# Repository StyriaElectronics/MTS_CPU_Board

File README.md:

# 🧠 MTS_CPU_Board

The **MTS_CPU_Board** is the central controller card for the **Modular Test System (MTS)**, built around the Raspberry Pi CM4.  
It serves as the master board for communication and control of all plug-in modules via the MTS backplane.

---

---

## 📦 Features

- 🧠 Raspberry Pi CM4 for computing and control
- 🔌 Backplane interface: UART, SPI, I²C, GPIO, CAN
- 🚀 EtherCAT interface for high-speed real-time data exchange
- 📡 Automatic plug-in module registration and configuration via CAN bus
- ⚡ Power input with regulation and monitoring
- 🌐 Optional Web UI (Flask based)

---

## 📁 Repository Structure

```
MTS_CPU_Board/
├── hardware/       → KiCad project files
├── software/       → UART daemons, webserver, protocols
├── docs/           → Block diagrams, pinouts, descriptions
├── images/         → Project photos and preview graphics
├── LICENSE         → Project license (CC BY 4.0)
├── .gitignore      → Exclude temp files (KiCad, Python, etc.)
└── README.md       → You are here
```

---

## 📷 Preview
**Todo**
> Add preview images to `images/preview.png`  
> and insert them like this:

```markdown

```

---

## 🛠 Usage Ideas

- Slot management for plug-in cards
- Monitoring voltages / temperatures
- Logging & remote access via web
- UART/CAN message routing
- High-speed real-time data logging and control via EtherCAT

---

## 📃 License

📢 Commercial Use Available

This project is licensed under the **Creative Commons Attribution-NonCommercial 4.0 International (CC BY-NC 4.0)**.

You may freely use, modify, and distribute this work for non-commercial purposes only, provided appropriate credit is given to the author.

➡️ Commercial use, including but not limited to:
  -	Integration into commercial products or services
	-	Redistribution or sale of derived products or components
	-	Commercial consulting or deployment

**is strictly prohibited without explicit written permission**

If you intend to use this project commercially, please contact me directly to negotiate a suitable license agreement.

📬 Contact: [andras.nagy@styria-electronics.at]
---

⚠️ **Disclaimer:**
This project is provided "as is" without warranty of any kind, either expressed or implied, including but not limited to fitness for a particular purpose, functionality, accuracy, or non-infringement. In no event shall the author(s) be liable for any claim, damages, or other liability arising from, out of, or in connection with the use or other dealings in this project.

## 🤝 Contributing

Contributions are welcome! Fork this repo and feel free to open pull requests or issues.

## 🚀 Status

🔧 In development – basic structure in place.  
More hardware and software coming soon.

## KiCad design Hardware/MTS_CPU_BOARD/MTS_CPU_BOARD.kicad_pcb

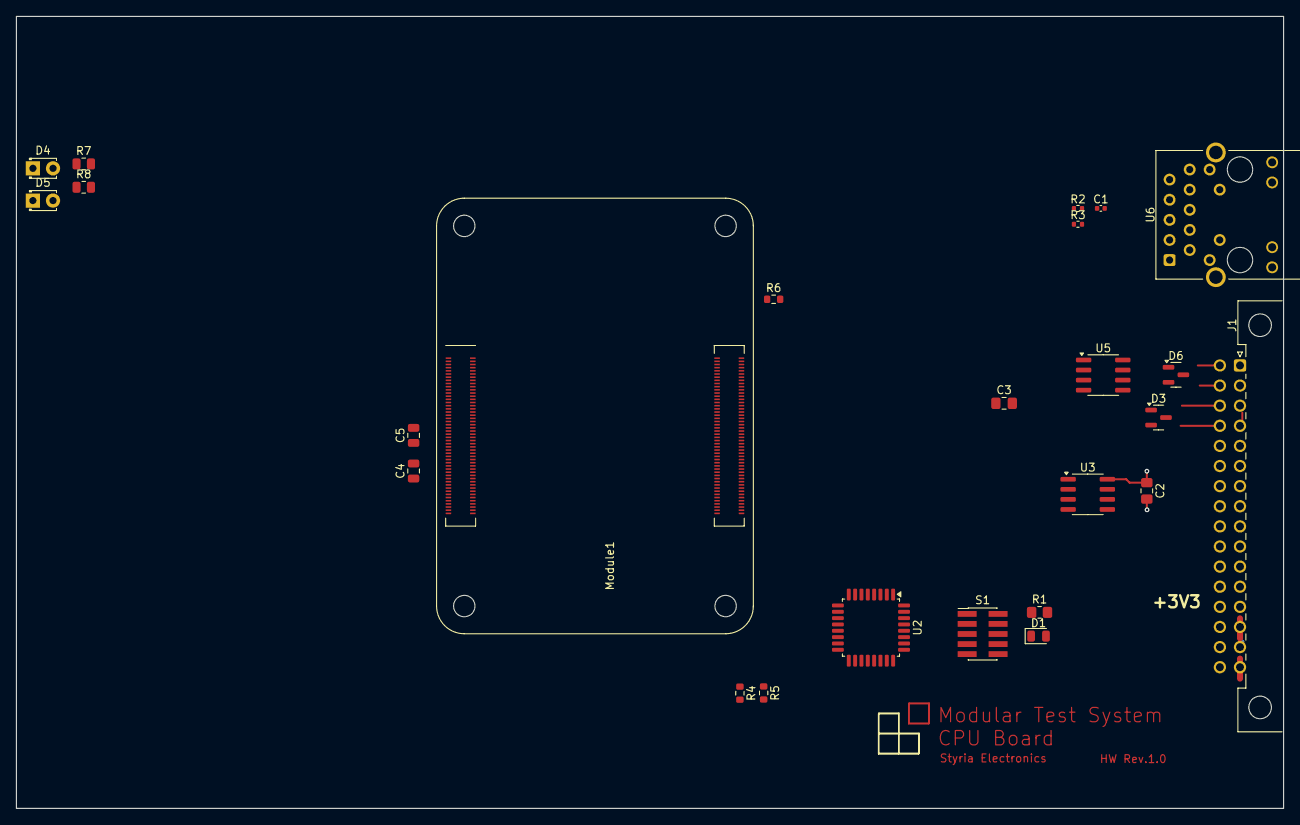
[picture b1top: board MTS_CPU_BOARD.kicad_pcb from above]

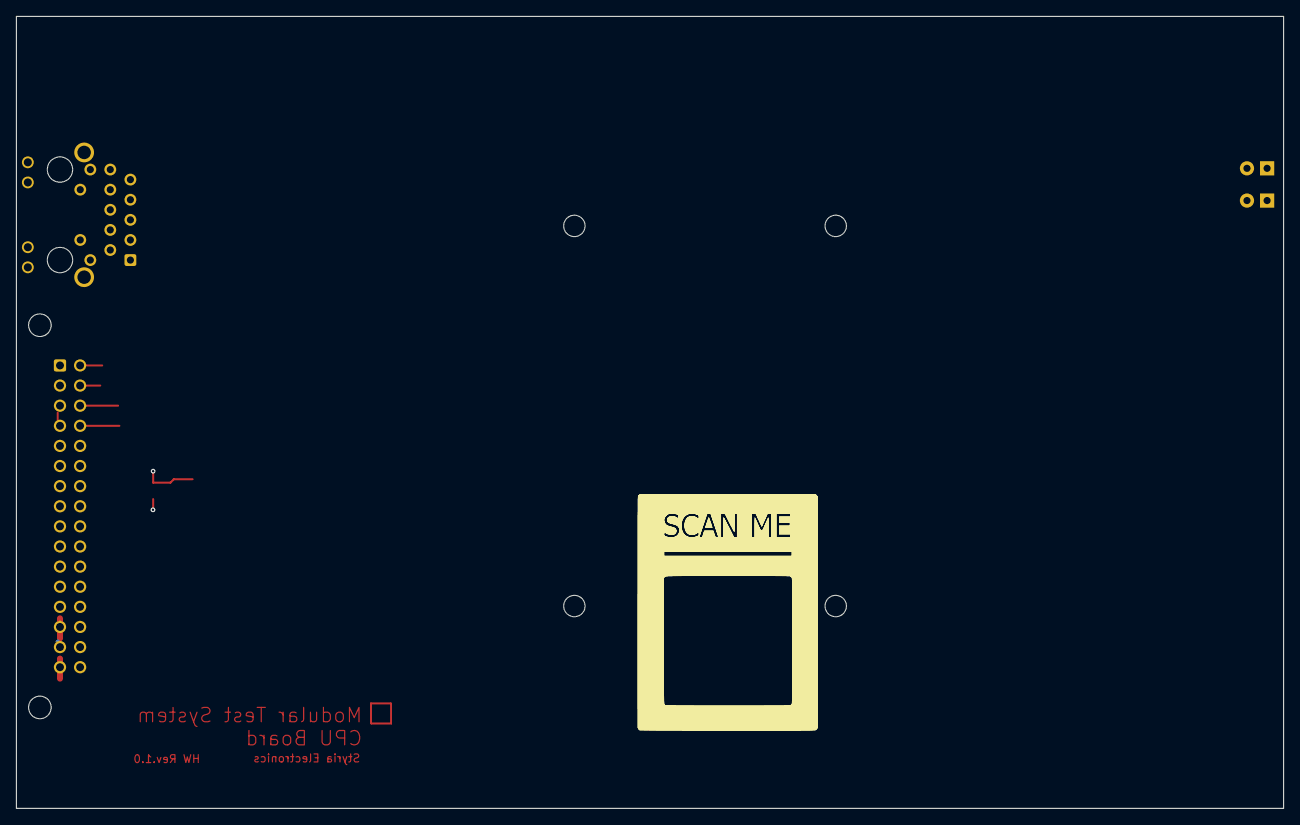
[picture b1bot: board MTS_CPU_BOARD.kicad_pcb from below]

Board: 6 copper layers, 160.0 x 100.0 mm, 27 parts (2 on the bottom side), 34 nets.

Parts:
C1: 100n; C_0402_1005Metric
C2, C3: 100n; C_0805_2012Metric_Pad1.18x1.45mm_HandSolder
C4, C5: 10u; C_0805_2012Metric
D1: Led1; LED_0805_2012Metric
D3, D6: PESD2CANFD24V-T; SOT-23
D4: RED; LED_D1.8mm_W3.3mm_H2.4mm
D5: GREEN; LED_D1.8mm_W3.3mm_H2.4mm
J1: DIN41612_02x16_ZB; DIN41612_B2_2x16_Male_Horizontal_THT
Module1: ComputeModule4-CM4; Raspberry-Pi-4-Compute-Module
QR Code: LOGO
QR Code#2: LOGO
R1: 680R; R_0805_2012Metric_Pad1.20x1.40mm_HandSolder
R2, R3: 470R; R_0402_1005Metric
R4, R5: 2K2; R_0603_1608Metric
R6: 2.2K; R_0603_1608Metric
R7, R8: 470R; R_0805_2012Metric
S1: SWD; PinHeader_2x05_P1.27mm_Vertical_SMD
U2: STM32G431K6Tx; LQFP-32_7x7mm_P0.8mm
U3: 24LC32; SOIC-8_3.9x4.9mm_P1.27mm
U5: TCAN337GDR; SOIC-8_3.9x4.9mm_P1.27mm
U6: MagJack-A70-112-331N126; TRJG0926HENL

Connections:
+3V3: C2.1, C3.1, D4.2 (A), D5.2 (A), Module1.78 (GPIO_VREF(1.8v/3.3v_Input)), R4.1, R5.1, S1.1, U2.1 (VDD), U2.15 (VDDA), U2.17 (VDD), U3.8 (VCC), U5.3 (VCC)
+3V3Ext: J1.a13 (Pin_z13), J1.a14 (Pin_z14)
+5V: C4.1, C5.1, Module1.77 (+5v_(Input)), Module1.79 (+5v_(Input)), Module1.81 (+5v_(Input)), Module1.83 (+5v_(Input)), Module1.85 (+5v_(Input)), Module1.87 (+5v_(Input))
+5VExt: J1.a15 (Pin_z15), J1.a16 (Pin_z16)
+12V: J1.a11 (Pin_z11), J1.a12 (Pin_z12)
-12V: J1.b11, J1.b12
/CM4/ETH_LEDG: Module1.17 (Ethernet_nLED2(3.3v)), R8.1
/CM4/ETH_LEDO: Module1.19 (Ethernet_nLED1(3.3v)), R7.1
/CM4/I2C_CLK_CM4: Module1.56 (GPIO3), R5.2
/CM4/I2C_SDA_CM4: Module1.58 (GPIO2), R4.2
/CM4/TRD0_N: J1.b8, Module1.10 (Ethernet_Pair0_N)
/CM4/TRD0_P: J1.b7, Module1.12 (Ethernet_Pair0_P)
/CM4/TRD1_N: J1.b10, Module1.6 (Ethernet_Pair1_N)
/CM4/TRD1_P: J1.b9, Module1.4 (Ethernet_Pair1_P)
/Ethernet/+3.3v: U6.15 (LEDG_A), U6.17 (LEDY_A)
/STM32/CANH: D6.1 (K), J1.b1, U5.7 (CANH)
/STM32/CANL: D6.2 (K), J1.b2, U5.6 (CANL)
CANFD_RX: U2.21 (PA11), U5.4 (RXD)
CANFD_TX: U2.22 (PA12), U5.1 (TXD)
GND: C1.2, C2.2, C3.2, C4.2, C5.2, D3.3 (A), D6.3 (A), J1.b13, J1.b14, J1.b15, J1.b16, Module1.1 (GND), Module1.2 (GND), Module1.7 (GND), Module1.8 (GND), Module1.13 (GND), Module1.14 (GND), Module1.22 (GND), Module1.23 (GND), Module1.32 (GND), Module1.33 (GND), Module1.42 (GND), Module1.43 (GND), Module1.52 (GND), Module1.53 (GND), Module1.59 (GND), Module1.60 (GND), Module1.65 (GND), Module1.66 (GND), Module1.71 (GND), Module1.74 (GND), Module1.98 (GND), Module1.107 (GND), Module1.108 (GND), Module1.113 (GND), Module1.114 (GND), Module1.119 (GND), Module1.120 (GND), Module1.125 (GND), Module1.126 (GND), Module1.131 (GND), Module1.132 (GND), Module1.137 (GND), Module1.138 (GND), Module1.144 (GND), Module1.150 (GND), Module1.155 (GND), Module1.156 (GND), Module1.161 (GND), Module1.162 (GND), Module1.167 (GND), Module1.168 (GND), Module1.173 (GND), Module1.174 (GND), Module1.179 (GND), Module1.180 (GND), Module1.185 (GND), Module1.186 (GND), Module1.191 (GND), Module1.192 (GND), Module1.197 (GND), Module1.198 (GND), R1.2, S1.3, S1.5, S1.9, U2.14 (VSSA), U2.16 (VSS), U2.32 (VSS), U3.1 (A0), U3.2 (A1), U3.3 (A2), U3.4 (GND), U5.2 (GND), U6.19 (SHIELD), U6.20 (SHIELD)
I2C_BUS_CLK: D3.2 (K), J1.b4
I2C_BUS_SDA: D3.1 (K), J1.b3
NRST: S1.10, U2.4 (PG10)
unnamed: C1.1, U6.4 (CT), U6.5 (CT)
unnamed: D1.2 (A), U2.13 (PB0)
unnamed: D1.1 (K), R1.1
unnamed: D4.1 (K), R7.2
unnamed: D5.1 (K), R8.2
unnamed: Module1.101 (USB_OTG_ID), R6.1
unnamed: R2.1, U6.16 (LEDG_K)
unnamed: R3.1, U6.18 (LEDY_K)
SWCLK: S1.4, U2.24 (PA14)
SWDIO: S1.2, U2.23 (PA13)
SWO: S1.6, U2.26 (PB3)

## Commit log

2025-04-07 Add base folder structure with .gitkeep files
2025-04-07 ADD Images gitkeep
2025-04-07 Update LICENSE
2025-04-07 Add Connector sheat
2025-04-07 Add some connectors
2025-04-23 Add EtherCAT
2025-04-24 Add status Led´s
